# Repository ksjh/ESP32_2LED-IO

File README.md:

A simple LED I/O board based on an [ESP32-C6 Super Mini](https://www.espboards.dev/esp32/esp32-c6-super-mini/) that allows to switch two LEDs and read back the current status.
It is just a quick solution for [Lange Nacht der Wissenschaften 2025](https://nacht-der-wissenschaften.de/) created in an afternoon alongside with some simple Arduino code to control the LEDs via USB CDC and a 3D printed case.

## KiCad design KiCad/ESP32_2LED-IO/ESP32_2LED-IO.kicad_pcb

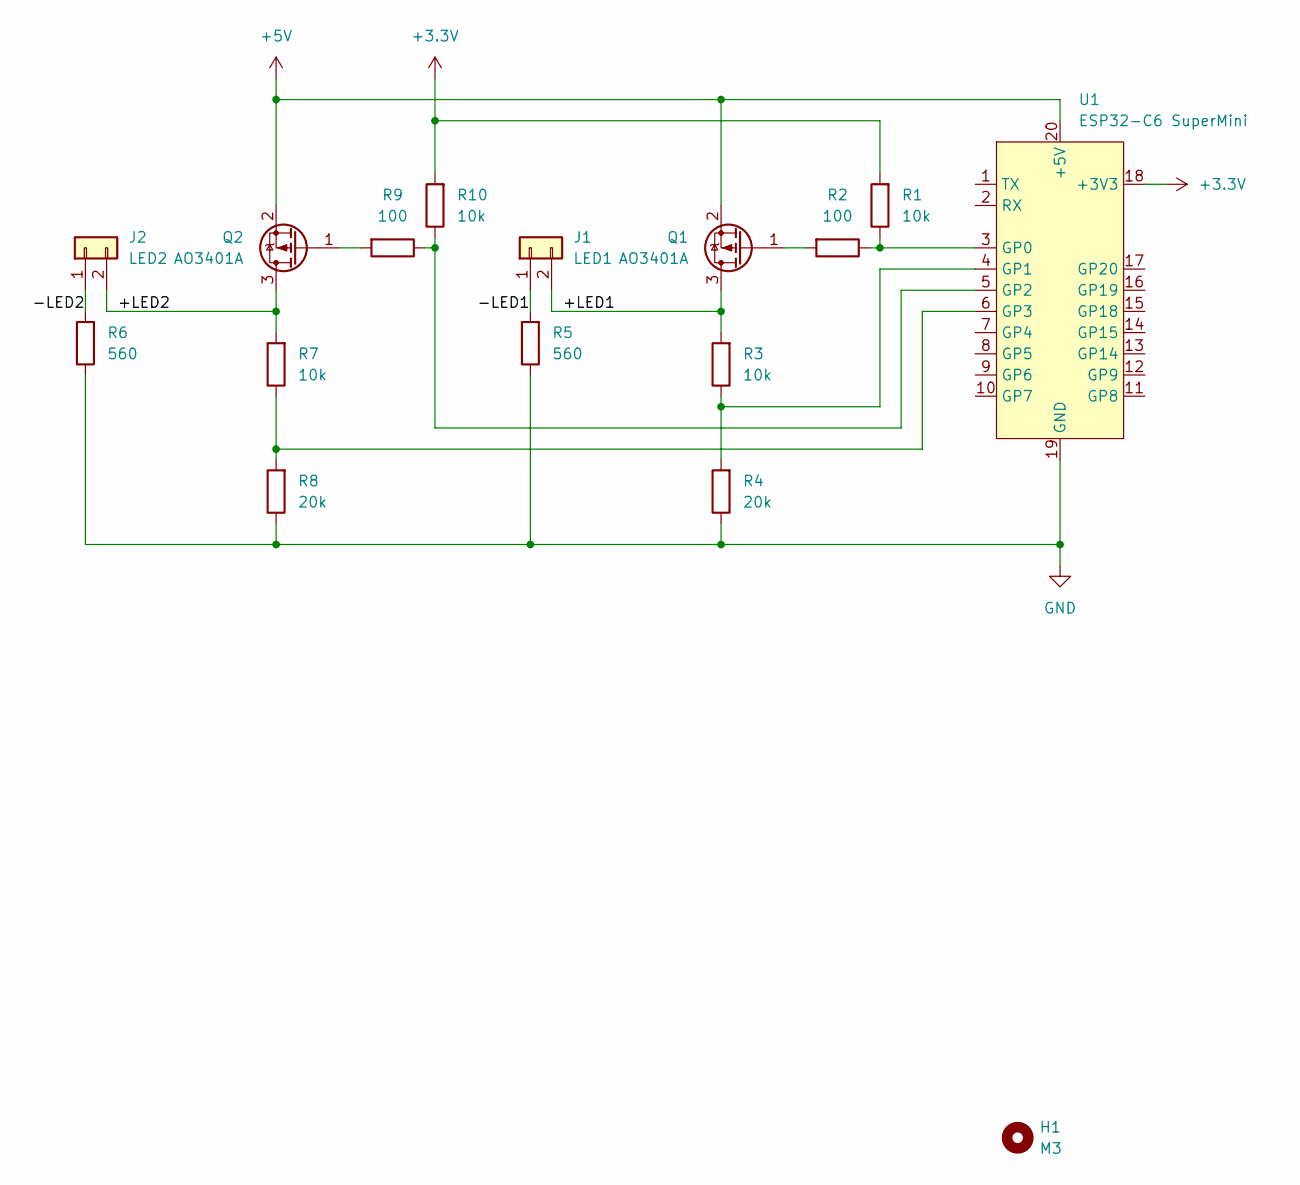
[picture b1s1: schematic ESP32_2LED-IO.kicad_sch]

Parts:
H1: M3; MountingHole_3.2mm_M3
J1: LED1; Molex_KK-254_AE-6410-02A_1x02_P2.54mm_Vertical
J2: LED2; Molex_KK-254_AE-6410-02A_1x02_P2.54mm_Vertical
Q1, Q2: AO3401A; SOT-23
R1, R3, R7, R10: 10k; R_0603_1608Metric_Pad0.98x0.95mm_HandSolder
R2, R9: 100; R_0603_1608Metric_Pad0.98x0.95mm_HandSolder
R4, R8: 20k; R_0603_1608Metric_Pad0.98x0.95mm_HandSolder
R5, R6: 560; R_1206_3216Metric_Pad1.30x1.75mm_HandSolder
U1: ESP32-C6 SuperMini; ESP32C6-SuperMini-SMD

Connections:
+3.3V: R1.2, R10.2, U1.18 (+3V3)
+5V: Q1.2 (S), Q2.2 (S), U1.20 (+5V)
/+LED1: J1.2, Q1.3 (D), R3.2
/+LED2: J2.2, Q2.3 (D), R7.2
/-LED1: J1.1, R5.2
/-LED2: J2.1, R6.2
GND: R4.1, R5.1, R6.1, R8.1, U1.19 (GND)
unnamed: Q1.1 (G), R2.2
unnamed: Q2.1 (G), R9.2
unnamed: R1.1, R2.1, U1.3 (GP0)
unnamed: R3.1, R4.2, U1.4 (GP1)
unnamed: R9.1, R10.1, U1.5 (GP2)
unnamed: R7.1, R8.2, U1.6 (GP3)

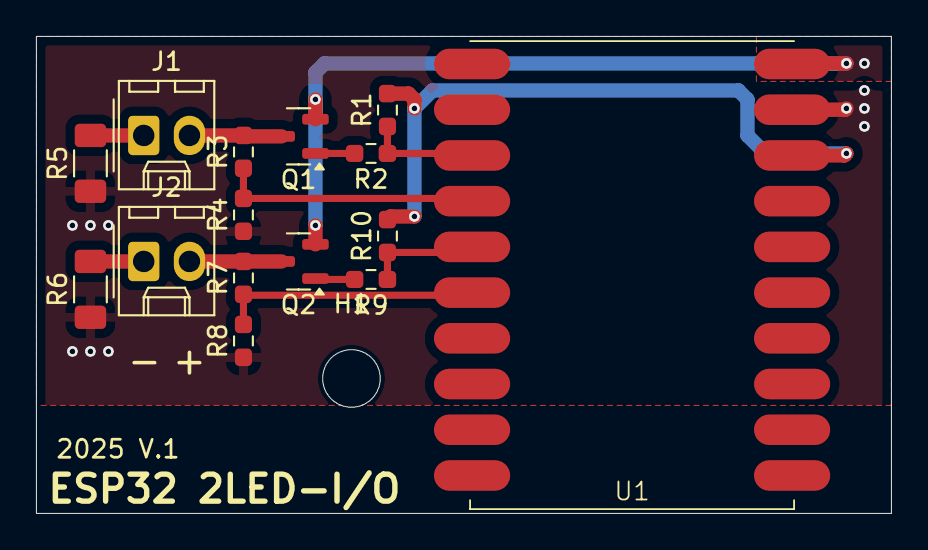
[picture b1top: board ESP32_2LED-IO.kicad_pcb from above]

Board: 2 copper layers, 47.5 x 26.5 mm, 16 parts (0 on the bottom side), 13 nets.

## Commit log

2025-09-13 Add licenses for exported KiCad symbols and footprints
2025-09-13 Fix OpenSCAD variable order
2025-09-13 Add optional thicker lid
2025-09-14 Arduino code cleanup
